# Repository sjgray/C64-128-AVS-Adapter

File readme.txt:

C64/C128 and Multi-System AVS Boards  by Steve J. Gray,  WWW.CBMSTEVE.CA
====================================

These are Commodore C64/C128 and Multi-System adapter boards based on
designs by Sven Petersen (https://github.com/svenpetersen1965?tab=repositories)
Sven has several designs for C64, C128 and VIC-20. These are separate boards
due to different DIN connectors, placement, and pinout differences. Also the
boards were designed with Eagle CAD.

My idea was first to combine the C64 and C128 boards into one by re-arranging
the RCA and S-VIDEO connectors to place them all at the top and hence allowing
the board to work on either machine. This is my "C64/C128" version.

The second idea was to make a board that could be configurable for different
systems. I added various solder-pad jumpers and added VIC-20, VIC-20 S-Video,
and Atari 8-bit configurations. This is the "Multi-System AVS" version.

Since I use Kicad I initially imported Sven's designs to get the proper part
footprints, and then working from there pretty much re-designed everything
for the new form factor(s) and options. I also added options for TRS connector
jacks for the Audio In, a connector for power output, and PH2.0 connector for
an additional video link cable to my C128 VGA15kHz+S-VIDEO 40/80 adapter
board (coming soon).

Designs
=======

V1:	- "C64/C128 AVS", for late model C64, 64C, C128, C16, SX-64 etc with DIN-8 video port.
	- Relocated connectors.
	- Power connector for +5V.
	- Made all jumpers 3-pin for headers or small switches (2.54mm spacing).
	- Not suitable for 3D printed case due to clearance issue.
	- Verified working.

V2:	- Now "Multi-System AVS".
	- Add support for VIC-20 (DIN-5)
	- Add support VIC-20 with Retro-Channel S-video adapter board (DIN-5).
	- Add support for Atari 8-bit (DIN-5) and chroma output.
	- Add support for U64 (DIN-8).
	- Move switches to top for easier access.
	- Add more clearance above DIN connector. Good for 3D case (Future).
	- Add TRS jacks for audio in.
	- Add header for cable to my C128 video adapter board.
	- Verified working.

GitHub
======

Designs are available here: https://github.com/sjgray/C64-128-AVS-Adapter

History
=======

2025-09-13 - Created C64/C128-AVS adapter
2025-09-22 - Created Github
2025-10-08 - Created Multi-System AVS completed
2025-11-29 - Tested ok, released V2 to Github

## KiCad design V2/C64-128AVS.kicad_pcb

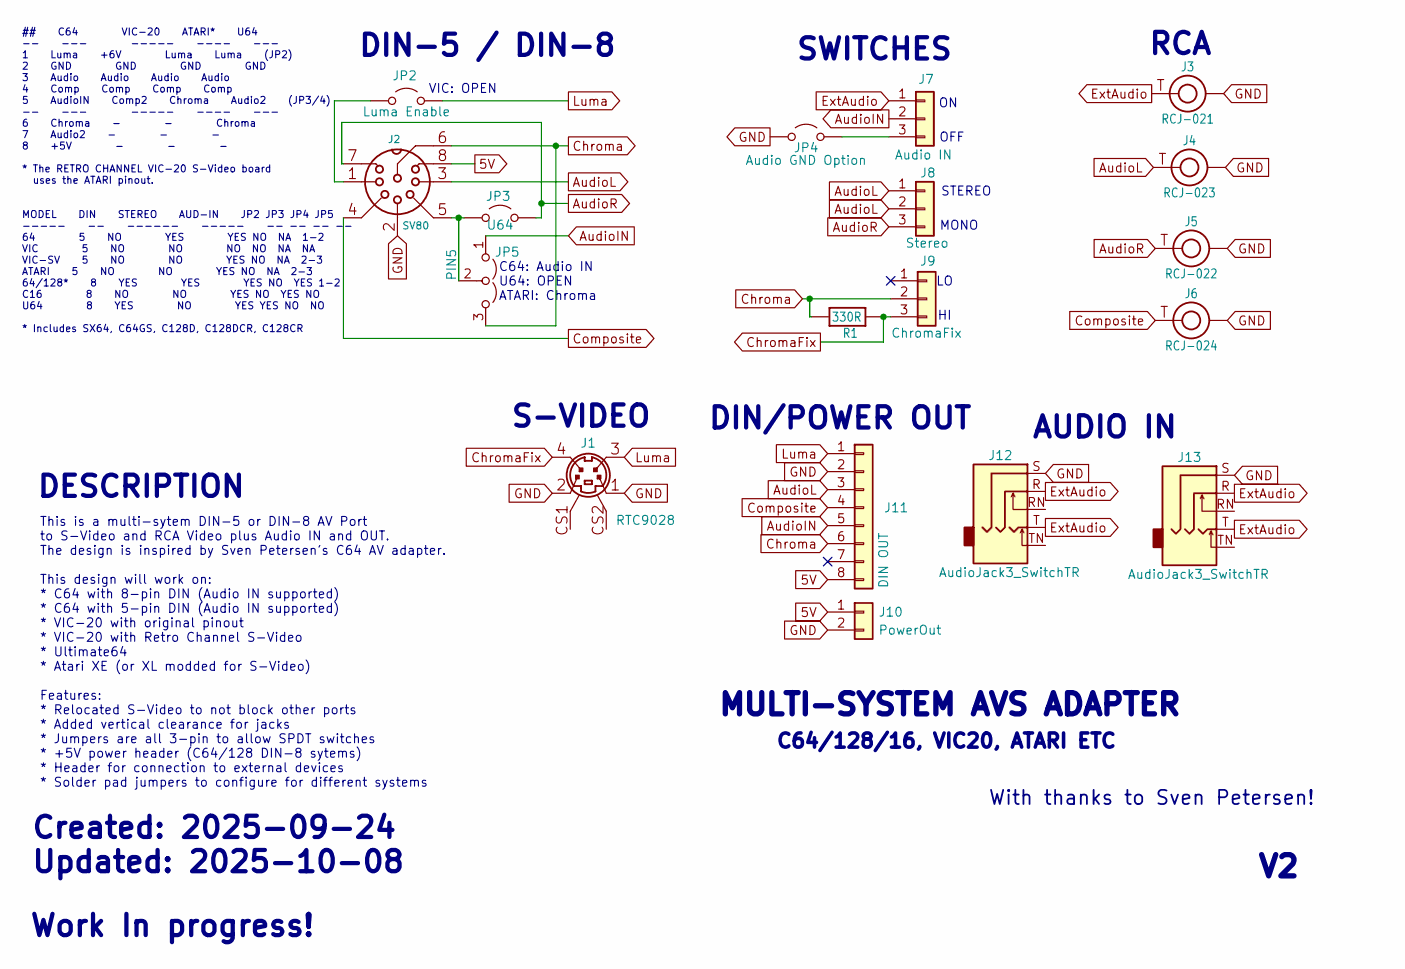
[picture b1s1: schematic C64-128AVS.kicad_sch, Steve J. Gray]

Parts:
J1: RTC9028; MINIDIN4_V
J2: SV80; SV80_INNER
J3: RCJ-021; RCJ-02X
J4: RCJ-023; RCJ-02X
J5: RCJ-022; RCJ-02X
J6: RCJ-024; RCJ-02X
J7: Audio IN; PinHeader_1x03_P2.54mm_Vertical
J8: Stereo; PinHeader_1x03_P2.54mm_Vertical
J9: ChromaFix; PinHeader_1x03_P2.54mm_Vertical
J10: PowerOut; PinHeader_1x02_P2.54mm_Vertical
J11: DIN OUT; PinHeader_1x08_P2.00mm_Vertical
J12, J13: AudioJack3_SwitchTR; Jack_3.5mm_CUI_PJ-358_vertical
JP2: Luma Enable; SolderJumper-2_P1.3mm_Open_RoundedPad1.0x1.5mm
JP3: U64; SolderJumper-2_P1.3mm_Open_RoundedPad1.0x1.5mm
JP4: Audio GND Option; SolderJumper-2_P1.3mm_Open_RoundedPad1.0x1.5mm
JP5: PIN5; SolderJumper-3_P1.3mm_Open_RoundedPad1.0x1.5mm
R1: 330R; R-10

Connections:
5V: J2.8, J10.1, J11.8
AudioIN: J7.2, J11.5, JP5.1 (A)
AudioL: J2.3, J4.T, J8.1, J8.2, J11.3
AudioR: J2.7, J5.T, J8.3, JP3.1 (A)
Chroma: J2.6, J9.2, J11.6, JP5.3 (B), R1.1
ChromaFix: J1.4, J9.3, R1.2
Composite: J2.4, J6.T, J11.4
ExtAudio: J3.T, J7.1, J12.R, J12.T, J13.R, J13.T
GND: J1.1, J1.2, J2.2, J3.R1 (R), J3.R2 (R), J4.R1 (R), J4.R2 (R), J5.R1 (R), J5.R2 (R), J6.R1 (R), J6.R2 (R), J10.2, J11.2, J12.S, J13.S, JP4.2 (B)
Luma: J1.3, J11.1, JP2.1 (A)
unnamed: J7.3, JP4.1 (A)
unnamed: J2.1, JP2.2 (B)
unnamed: J2.5, JP3.2 (B), JP5.2 (C)

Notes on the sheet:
VIC: OPEN
Work In progress!
MULTI-SYSTEM AVS ADAPTER
This is a multi-sytem DIN-5 or DIN-8 AV Port to S-Video and RCA Video plus Audio IN and OUT. The design is inspired by Sven Petersen's C64 AV adapter. This design will work on: * C64 with 8-pin DIN (Audio IN supported) * C64 with 5-pin DIN (Audio IN supported) * VIC-20 with original pinout * VIC-20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
MONO
OFF
C64/128/16, VIC20, ATARI ETC
DIN/POWER OUT
RCA
SWITCHES
DIN-5 / DIN-8
Created: 2025-09-24 Updated: 2025-10-08
STEREO
AUDIO IN
C64: Audio IN U64: OPEN ATARI: Chroma
## C64 VIC-20 ATARI* U64 -- --- ----- ---- --- 1 Luma +6V Luma Luma (JP2) 2 GND GND GND GND 3 Audio Audio Audio Audio 4 Comp Comp Comp Comp 5 AudioIN Comp2 Chroma Audio2 (JP3/4) -- --- ----- ---- --- 6 Chroma - - Chroma 7 Audio2 - - - 8 +5V - - - * The RETRO CHANNEL VIC-20 S-Video board uses the AT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
With thanks to Sven Petersen!
DESCRIPTION
S-VIDEO

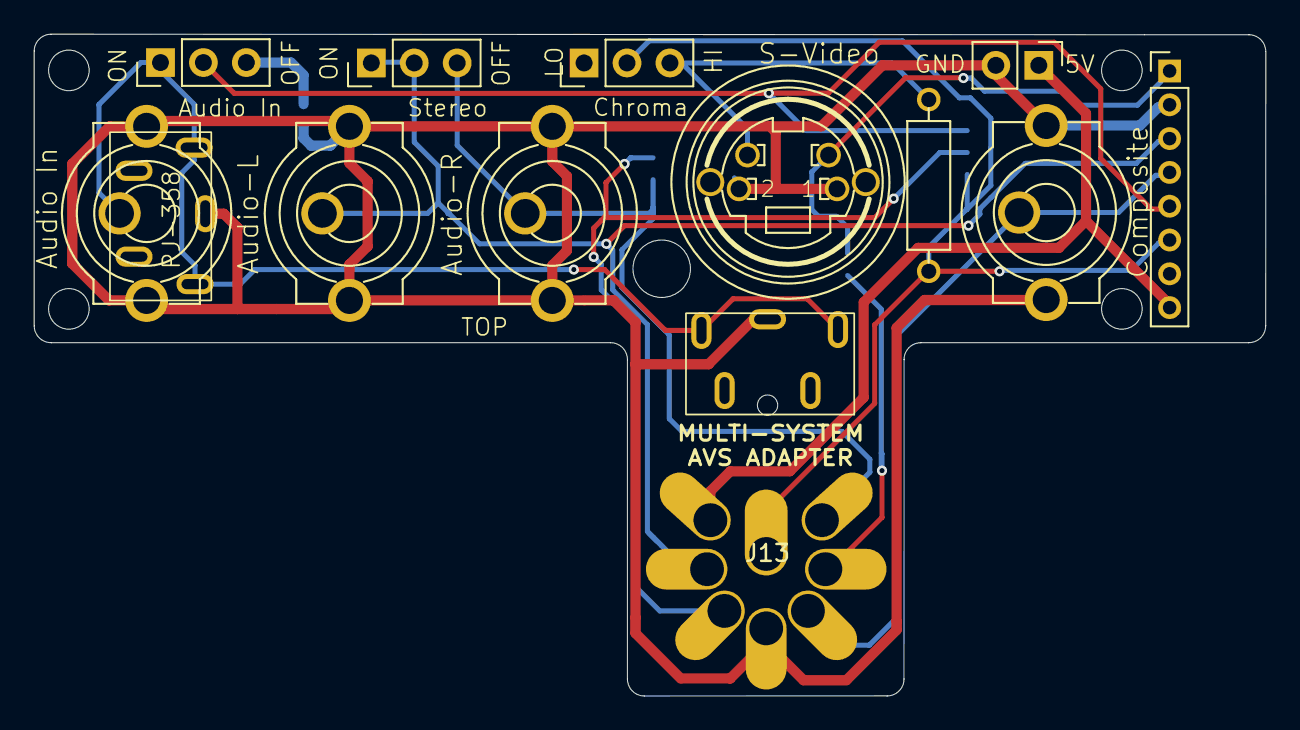
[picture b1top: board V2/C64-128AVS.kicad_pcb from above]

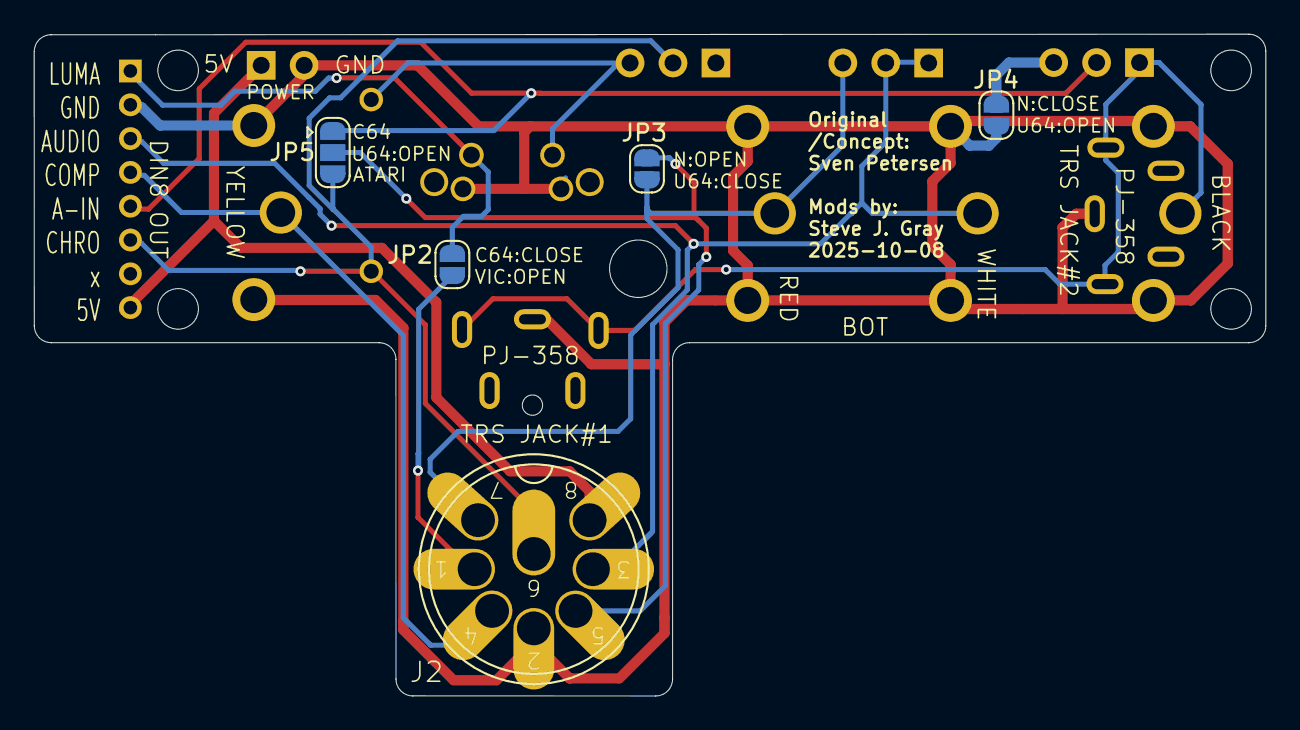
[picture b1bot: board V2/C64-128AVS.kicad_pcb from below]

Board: 2 copper layers, 72.9 x 39.2 mm, 18 parts (5 on the bottom side), 13 nets.

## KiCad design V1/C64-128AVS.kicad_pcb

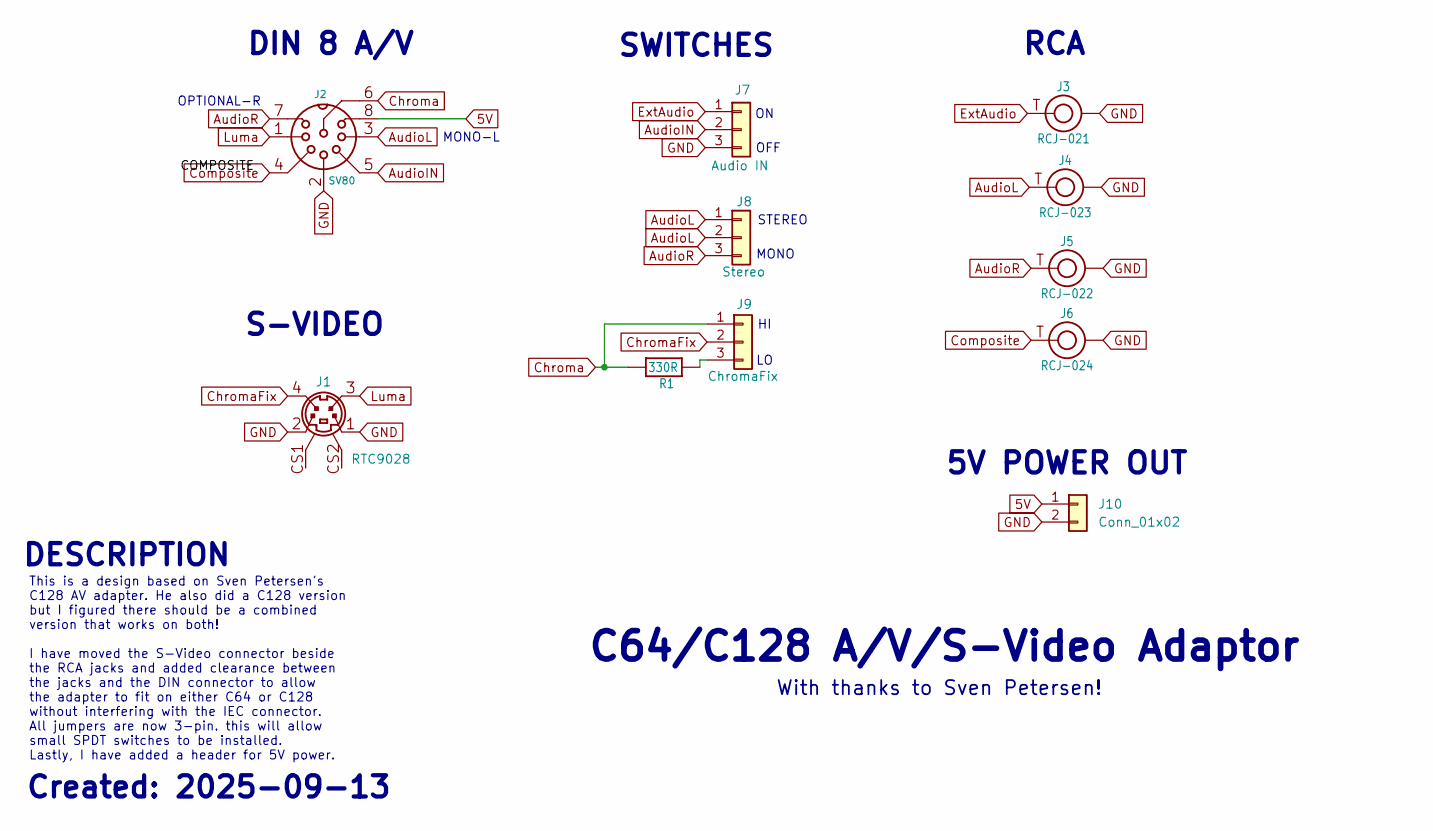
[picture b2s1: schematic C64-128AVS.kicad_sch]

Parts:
J1: RTC9028; MINIDIN4_V
J2: SV80; SV80_INNER
J3: RCJ-021; RCJ-02X
J4: RCJ-023; RCJ-02X
J5: RCJ-022; RCJ-02X
J6: RCJ-024; RCJ-02X
J7: Audio IN; PinHeader_1x03_P2.54mm_Vertical
J8: Stereo; PinHeader_1x03_P2.54mm_Vertical
J9: ChromaFix; PinHeader_1x03_P2.54mm_Vertical
J10: Conn_01x02; PinHeader_1x02_P2.54mm_Vertical
R1: 330R; R-10

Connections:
5V: J2.8, J10.1
AudioIN: J2.5, J7.2
AudioL: J2.3, J4.T, J8.1, J8.2
AudioR: J2.7, J5.T, J8.3
Chroma: J2.6, J9.1, R1.1
ChromaFix: J1.4, J9.2
Composite: J2.4, J6.T
ExtAudio: J3.T, J7.1
GND: J1.1, J1.2, J2.2, J3.R1 (R), J3.R2 (R), J4.R1 (R), J4.R2 (R), J5.R1 (R), J5.R2 (R), J6.R1 (R), J6.R2 (R), J7.3, J10.2
Luma: J1.3, J2.1
unnamed: J9.3, R1.2

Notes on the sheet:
OPTIONAL-R
C64/C128 A/V/S-Video Adaptor
This is a design based on Sven Petersen's C128 AV adapter. He also did a C128 version but I figured there should be a combined version that works on both! I have moved the S-Video connector beside the RCA jacks and added clearance between the jacks and the DIN connector to allow the adapter to fit 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
MONO
5V POWER OUT
OFF
RCA
MONO-L
SWITCHES
DIN 8 A/V
Created: 2025-09-13
STEREO
With thanks to Sven Petersen!
DESCRIPTION
S-VIDEO

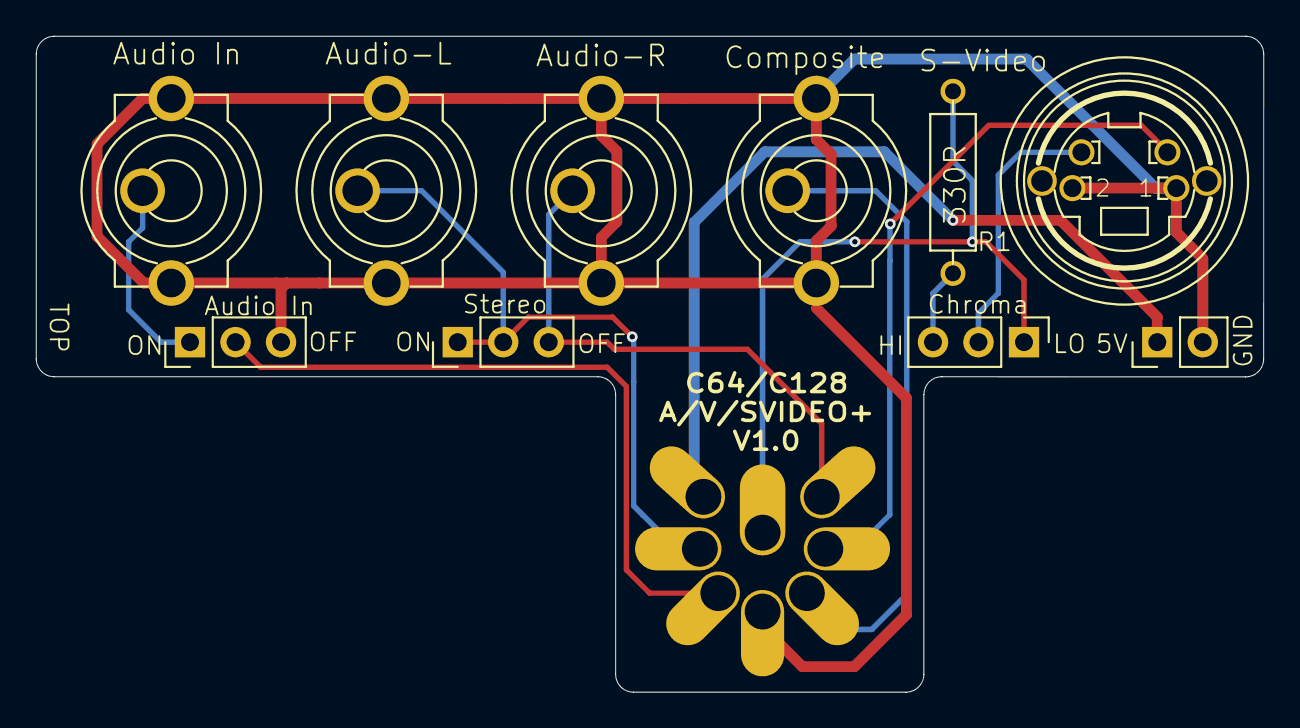
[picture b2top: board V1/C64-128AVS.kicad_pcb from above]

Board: 2 copper layers, 68.5 x 36.6 mm, 11 parts (1 on the bottom side), 11 nets.

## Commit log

2025-09-23 V1 release
    Thanks to Sven Petersen for the initial C64 design. Converted to Kicad and modified to work on both C64 and C128. C64 must be 8-pin DIN. Note some C64 do not supply power but can be fixed with a smal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
2025-09-23 Add readme to main folder
    Add readme to main folder.
2025-09-23 Reduce picture res
    Reduce picture res
2025-09-23 Update schematic and add BOM
    Updated schematic to add working status. Add interactive BOM.
2025-11-30 Add V2 "Multi-System AVS" board
    Fix clearance, add support for VIC-20, VIC-20 S-Video, and Atari 8-bit systems with DIN-5. Add support for U64. Add TRS audio jacks, configuration jumpers and 8-pin signal header. Move switches to th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
2025-12-09 Add V2 BOM
    I sourced all my parts from AliExpress except common parts like headers, resistors etc.
2025-12-10 Add V2 Interactive BOM
    Add V2 Interactive BOM.
